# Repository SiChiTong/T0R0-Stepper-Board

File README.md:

# T0R0-Stepper-Board
Stepper Motor Driver Based on STM32F446 and dual L6208 motor driver

Datasheet of MCU  [MCU]
[MCU]: https://www.st.com/resource/en/datasheet/stm32f446re.pdf

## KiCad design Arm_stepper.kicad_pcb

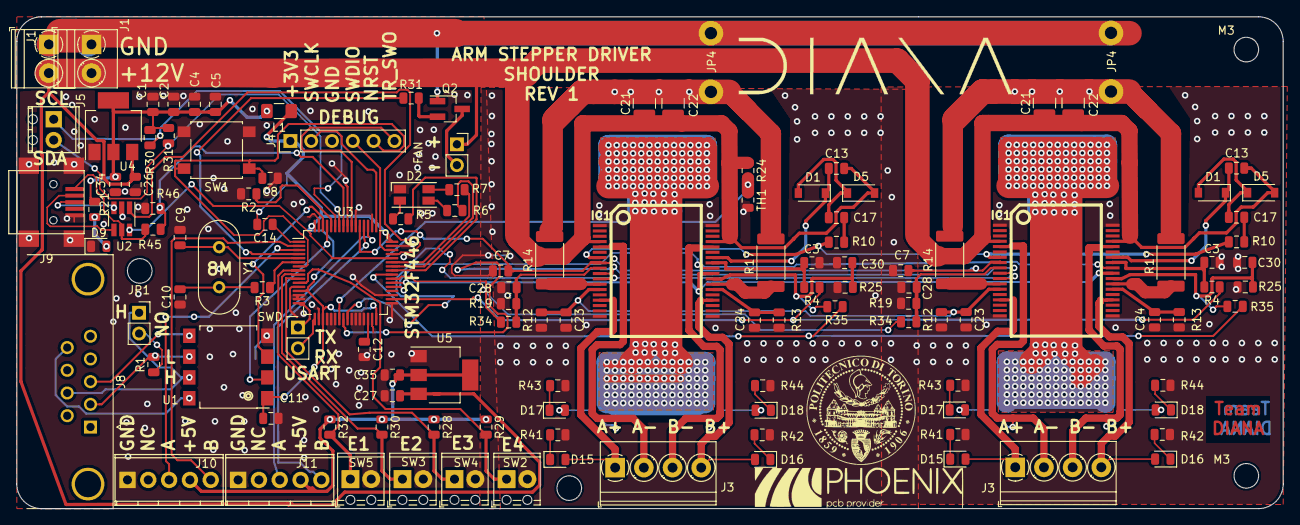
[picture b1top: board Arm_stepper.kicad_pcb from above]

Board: 2 copper layers, 154.5 x 60.0 mm, 126 parts (0 on the bottom side), 79 nets.

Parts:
C1, C2, C4, C5, C7, C7#2, C26, C27, C34, C35: 100nF; C_0805_2012Metric
C3, C3#2: 5.6n; C_0805_2012Metric
C8, C14: 100n; C_0805_2012Metric
C9, C10: 20pF; C_0805_2012Metric
C11, C12: 2.2uF; C_0805_2012Metric
C13, C13#2: 220nF1; C_0805_2012Metric
C17, C17#2: 10nF; C_0805_2012Metric
C21, C21#2: 100nF; C_1210_3225Metric
C22, C22#2: 100uF ceramic; C_1210_3225Metric
C23, C23#2, C24, C24#2: 1nF; C_0805_2012Metric
C28, C28#2, C30, C30#2: 68nF; C_0805_2012Metric
D1, D1#2, D5, D5#2: 1N4148; D_SOD-123
D2: LED_CRGB; LED_RGB_1210
D9: LED_RED; LED_0805_2012Metric
D15, D15#2, D16, D16#2, D17, D17#2, D18, D18#2: LED; LED_0805_2012Metric
FAN: Fan; PinSocket_1x02_P2.54mm_Vertical
IC1, IC1#2: L6208D; POWERSO36
J1, J1#2: 12V_CONN; TerminalBlock_Phoenix_PT-1,5-2-3.5-H_1x02_P3.50mm_Horizontal
J3, J3#2: M1_CONN; TerminalBlock_Phoenix_PT-1,5-4-3.5-H_1x04_P3.50mm_Horizontal
J4: Conn_01x06_Male; PinHeader_1x06_P2.54mm_Vertical
J5: I2C_CONN; TerminalBlock_Phoenix_MPT-2.54mm_2pol
J8: Conn_01x04_Female; DSUB-9_Female_Horizontal_P2.77x2.84mm_EdgePinOffset4.94mm_H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
J9: USB_B_Mini; USB_Mini-B
J10: ENCODER1; TerminalBlock_Phoenix_MPT-2.54mm_5pol
J11: ENCODER2; TerminalBlock_Phoenix_MPT-2.54mm_5pol
JP1: Jumper_NO_Small; PinSocket_1x02_P2.54mm_Vertical
JP4, JP4#2: SolderJumper_2_Bridged; WireConnection_1.50mmDrill
L1: L; L_1206_3216Metric_Pad1.42x1.75mm_HandSolder
M3, M3#2: MountingHole_3mm
Q2: 2N2219; SOT-23_Handsoldering
R1: 120; R_0805_2012Metric
R2, R5, R6, R7, R28, R29, R30#2, R32: 10k; R_0805_2012Metric
R3, R21, R30, R31: 1k; R_0805_2012Metric
R4, R4#2: 100k; R_0805_2012Metric
R10, R10#2: 100; R_0805_2012Metric
R12, R12#2, R13, R13#2: 39k; R_0805_2012Metric
R14, R14#2, R17, R17#2: 0.3; R_2512_6332Metric
R19, R19#2, R25, R25#2: 2.2K; R_0805_2012Metric
R24: 27K; R_0805_2012Metric
R31#2: 70k; R_0805_2012Metric
R34, R34#2, R35, R35#2: 4.7K; R_0805_2012Metric
R41, R41#2, R42, R42#2, R43, R43#2, R44, R44#2: 10K; R_0805_2012Metric
R45: 47K; R_0805_2012Metric
R46: 68K; R_0805_2012Metric
SW1: SW_Push_Dual; SW_SPST_B3S-1000
SW2: endstop4; TerminalBlock_Phoenix_MPT-0,5-2-2.54_1x02_P2.54mm_Horizontal
SW3: endstop1; TerminalBlock_Phoenix_MPT-0,5-2-2.54_1x02_P2.54mm_Horizontal
SW4: endstop3; TerminalBlock_Phoenix_MPT-0,5-2-2.54_1x02_P2.54mm_Horizontal
SW5: endstop2; TerminalBlock_Phoenix_MPT-0,5-2-2.54_1x02_P2.54mm_Horizontal
SWD: Pin_Header_Straight_1x02_Pitch2.54mm
TH1: 10k+30T; R_0805_2012Metric
U1: ISO1050-00_isolation; SSO-8_6.7x9.8mm_P2.54mm_Clearance8mm
U2: USBLC6-2SC6; SOT-23-6_Handsoldering
U3: STM32F446RETx; LQFP-64_10x10mm_P0.5mm
U4: LM1117-3.3; SOT-223-3_TabPin2
U5: LM1117-5; SOT-223-3_TabPin2
Y1: 8Mhz; Crystal_HC49-4H_Vertical

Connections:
+3V3: C1.2, C2.2, C4.2, C5.2, C11.1, C14.2, C34.1, J4.1, L1.1, L1.2, R21.2, R30.2, R31.2, U1.1, U3.13, U3.19, U3.32, U3.48, U3.64, U4.2
+5V: C35.1, J10.4, J11.4, R28.1, R29.1, R30#2.1, R32.1, U5.2
+12V: C13.1, C13#2.1, C21.1, C21#2.1, C22.1, C22#2.1, C26.1, C27.1, D5.2, D5#2.2, FAN.1, IC1.4, IC1.33, IC1#2.4, IC1#2.33, J1.2, J1#2.2, R24.1, U4.3, U5.3
/+5v_can: J8.9, U1.8
/M2_A+: D15.2, D15#2.2, IC1.15, IC1#2.15, J3.1, J3#2.1
/M2_A-: D17.2, D17#2.2, IC1.5, IC1#2.5, J3.2, J3#2.2
/M2_B+: D16.2, D16#2.2, IC1.22, IC1#2.22, J3.4, J3#2.4
/M2_B-: D18.2, D18#2.2, IC1.32, IC1#2.32, J3.3, J3#2.3
/NRST: C8.2, J4.5, SW1.1, U3.7
/SWCLK: J4.2, U3.49
/SWDIO: J4.4, U3.46
/TRACESWO: J4.6, U3.55
/gnd_can: J8.3, U1.5
CAN_RX: U1.2, U3.61
CAN_TX: U1.3, U3.62
CLK1: IC1.10, IC1#2.10, U3.24
CRTL1: IC1.28, IC1#2.28, U3.37
CW1: IC1.11, IC1#2.11, U3.25
E1: R32.2, SW5.1, U3.8
E1_1: J10.5, U3.2
E1_2: J10.3, U3.3
E2: R30#2.2, SW3.1, U3.9
E2_1: J11.5, U3.52
E2_2: J11.3, U3.51
E3: R28.2, SW4.1, U3.10
E4: R29.2, SW2.1, U3.11
EN1: R4.1, R4#2.1, U3.34
FAN: R31#2.1, U3.4
GNDD: IC1.37, IC1#2.37
GNDPWR: J1.1, J1#2.1, JP4.1, JP4#2.1, Q2.1
GNDS: C1.1, C2.1, C3.2, C3#2.2, C4.1, C5.1, C7.2, C7#2.2, C8.1, C9.2, C10.1, C11.2, C12.2, C21.2, C21#2.2, C22.2, C22#2.2, C23.2, C23#2.2, C24.2, C24#2.2, C26.2, C27.2, C28.1, C28#2.1, C30.1, C30#2.1, C34.2, C35.2, D2.1, D9.1, IC1.1, IC1.18, IC1.19, IC1.36, IC1#2.1, IC1#2.18, IC1#2.19, IC1#2.36, J4.3, J9.5, J9.6, J10.1, J11.1, JP4.2, JP4#2.2, R2.2, R12.1, R12#2.1, R13.1, R13#2.1, R14.2, R14#2.2, R17.2, R17#2.2, R19.1, R19#2.1, R25.1, R25#2.1, R41.1, R41#2.1, R42.1, R42#2.1, R43.1, R43#2.1, R44.1, R44#2.1, R46.2, SW1.2, SW2.2, SW3.2, SW4.2, SW5.2, TH1.2, U1.4, U2.2, U3.12, U3.14, U3.15, U3.18, U3.20, U3.21, U3.22, U3.26, U3.27, U3.28, U3.29, U3.31, U3.33, U3.35, U3.47, U3.50, U3.54, U3.56, U3.63, U4.1, U5.1
HALF1: IC1.27, IC1#2.27, U3.38
I1: SWD.1, U3.16
I2: SWD.2, U3.17
unnamed: C3.1, C3#2.1, IC1.29, IC1#2.29, R4.2, R4#2.2
unnamed: C9.1, U3.5, Y1.1
unnamed: C10.2, R3.2, Y1.2
unnamed: C12.1, U3.30
unnamed: C13.2, C13#2.2, D1.1, D1#2.1, IC1.30, IC1#2.30
unnamed: C14.1, U3.1
unnamed: C17.1, C17#2.1, D1.2, D1#2.2, D5.1, D5#2.1
unnamed: C17.2, C17#2.2, R10.2, R10#2.2
unnamed: C23.1, C23#2.1, IC1.13, IC1#2.13, R12.2, R12#2.2
unnamed: C24.1, C24#2.1, IC1.24, IC1#2.24, R13.2, R13#2.2
unnamed: C28.2, C28#2.2, IC1.9, IC1#2.9, R19.2, R19#2.2, R34.1, R34#2.1
unnamed: C30.2, C30#2.2, IC1.26, IC1#2.26, R25.2, R25#2.2, R35.1, R35#2.1
unnamed: D2.2, R5.1
unnamed: D2.3, R6.1
unnamed: D2.4, R7.1
unnamed: D9.2, R21.1
unnamed: D15.1, D15#2.1, R41.2, R41#2.2
unnamed: D16.1, D16#2.1, R42.2, R42#2.2
unnamed: D17.1, D17#2.1, R43.2, R43#2.2
unnamed: D18.1, D18#2.1, R44.2, R44#2.2
unnamed: IC1.7, IC1#2.7, R10.1, R10#2.1
unnamed: IC1.12, IC1#2.12, R14.1, R14#2.1
unnamed: IC1.25, IC1#2.25, R17.1, R17#2.1
unnamed: J8.7, JP1.1, U1.7
unnamed: J8.2, R1.2, U1.6
unnamed: J9.1, R45.1, U2.5
unnamed: J9.2, U2.4
unnamed: J9.3, U2.3
unnamed: JP1.2, R1.1
unnamed: FAN.2, Q2.3
unnamed: Q2.2, R31#2.2
unnamed: R2.1, U3.60
unnamed: R3.1, U3.6
unnamed: R5.2, U3.41
unnamed: R6.2, U3.42
unnamed: R7.2, U3.43
PWMA1: R34.2, R34#2.2, U3.39
PWMB1: R35.2, R35#2.2, U3.40
RST1: C7.1, C7#2.1, IC1.8, IC1#2.8, U3.53
USB_DM: U2.6, U3.44
USB_DP: U2.1, U3.45
USB_EN: R45.2, R46.1, U3.57
i2C1_SCL: J5.2, R31.1, U3.58
i2C1_SDA: J5.1, R30.1, U3.59
t_SENS: R24.2, TH1.1, U3.23

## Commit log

2019-03-22 init
2019-03-25 fixx
2019-04-01 gerber
